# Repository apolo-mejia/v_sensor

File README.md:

# v_sensor
Estos son archivos del sensor de vibraciones desarrollado en el entorno del proyecto Siracuza:
Los archivos que contiene:
- Archivos de diseño electrónico: Esquematicos, planchas de los PCBs y librerias delos componentes,
- Códigos de programación del micro-procesador,
- Archivos de diseño de la carcaza.

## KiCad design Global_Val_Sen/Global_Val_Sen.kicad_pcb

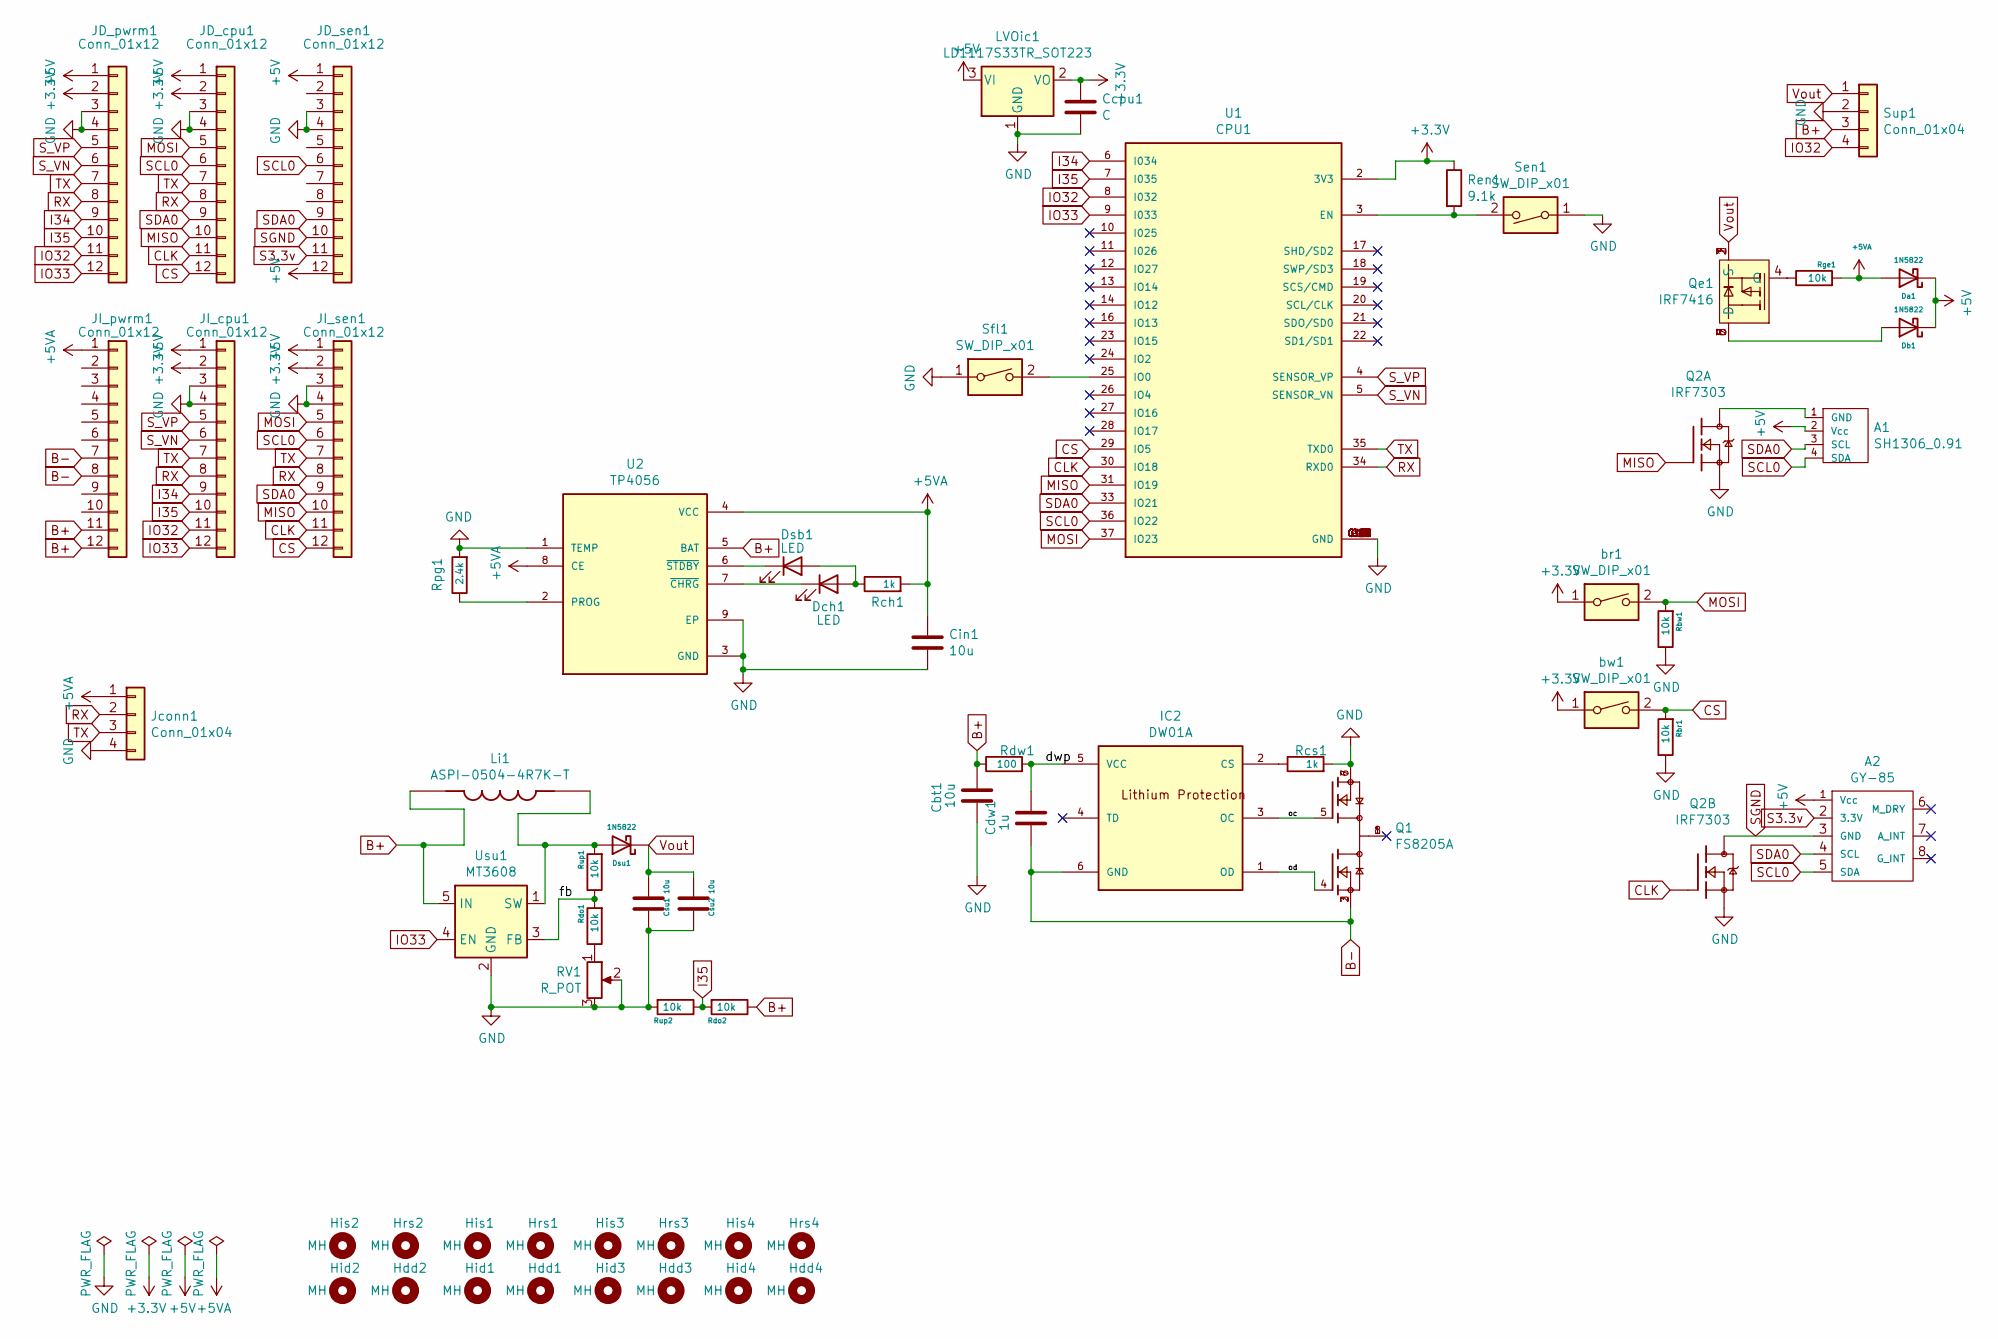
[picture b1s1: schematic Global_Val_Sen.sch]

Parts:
A1: SH1306_0.91; SSD1306-0.91-OLED-4pin-128x32
A2: GY-85
Cbt1: 10u; CP_EIA-3216-10_Kemet-I_Pad1.58x1.35mm_HandSolder
Ccpu1: C; CP_EIA-3216-10_Kemet-I_Pad1.58x1.35mm_HandSolder
Cdw1: 1u; CP_EIA-3216-10_Kemet-I_Pad1.58x1.35mm_HandSolder
Cin1: 10u; CP_EIA-3216-10_Kemet-I_Pad1.58x1.35mm_HandSolder
Csu1, Csu2: 10u; CP_EIA-3216-10_Kemet-I_Pad1.58x1.35mm_HandSolder
Da1: 1N5822; D_SMA
Db1: 1N5822; D_SMA
Dch1: LED; LED_1206_3216Metric_Castellated
Dsb1: LED; LED_1206_3216Metric_Castellated
Dsu1: 1N5822; D_SMA
Hdd1, Hdd2, Hdd3, Hdd4: MH; MountingHole_2.2mm_M2_DIN965
Hid1, Hid2, Hid3, Hid4: MH; MountingHole_2.2mm_M2_DIN965
His1, His2, His3, His4: MH; MountingHole_2.2mm_M2_DIN965
Hrs1, Hrs2, Hrs3, Hrs4: MH; MountingHole_2.2mm_M2_DIN965
IC2: DW01A; SOT-23-6_Handsoldering
JD_cpu1: Conn_01x12; PinSocket_1x12_P2.00mm_Vertical
JD_pwrm1: Conn_01x12; PinSocket_1x12_P2.00mm_Vertical
JD_sen1: Conn_01x12; PinSocket_1x12_P2.00mm_Vertical
JI_cpu1: Conn_01x12; PinSocket_1x12_P2.00mm_Vertical
JI_pwrm1: Conn_01x12; PinSocket_1x12_P2.00mm_Vertical
JI_sen1: Conn_01x12; PinSocket_1x12_P2.00mm_Vertical
Jconn1: Conn_01x04; PinHeader_1x04_P2.00mm_Vertical
LVOic1: LD1117S33TR_SOT223; SOT-223-3_TabPin2
Li1: ASPI-0504-4R7K-T; IND_ASPI-0504-4R7K-T; PARTREV 06.24.13
Q1: FS8205A; SOP65P640X120-8N; PARTREV 1.7
Q2: IRF7303; SOIC-8
Qe1: IRF7416; SO-8_3.9x4.9mm_P1.27mm
RV1: R_POT; Potentiometer_Bourns_TC33X_Vertical
Rbr1: 10k; R_1206_3216Metric_Pad1.30x1.75mm_HandSolder
Rbw1: 10k; R_1206_3216Metric_Pad1.30x1.75mm_HandSolder
Rch1: 1k; R_1206_3216Metric_Pad1.30x1.75mm_HandSolder
Rcs1: 1k; R_1206_3216Metric_Pad1.30x1.75mm_HandSolder
Rdo1, Rdo2: 10k; R_1206_3216Metric_Pad1.30x1.75mm_HandSolder
Rdw1: 100; R_1206_3216Metric_Pad1.30x1.75mm_HandSolder
Ren1: 9.1k; R_1206_3216Metric_Pad1.30x1.75mm_HandSolder
Rge1: 10k; R_1206_3216Metric_Pad1.30x1.75mm_HandSolder
Rpg1: 2.4k; R_1206_3216Metric_Pad1.30x1.75mm_HandSolder
Rup1, Rup2: 10k; R_1206_3216Metric_Pad1.30x1.75mm_HandSolder
Sen1: SW_DIP_x01; SW_SPST_CK_RS282G05A3
Sfl1: SW_DIP_x01; SW_SPST_CK_RS282G05A3
Sup1: Conn_01x04; PinSocket_1x04_P2.54mm_Vertical
U1: CPU1; ESP32-WROOM-32U; PARTREV V1.9
U2: TP4056; SOP127P600X175-9N
Usu1: MT3608; SOT-23-6
br1: SW_DIP_x01; SW_SPST_CK_RS282G05A3
bw1: SW_DIP_x01; SW_SPST_CK_RS282G05A3

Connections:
+3V3: Ccpu1.1, JD_cpu1.2, JD_pwrm1.2, JI_cpu1.2, JI_sen1.2, LVOic1.2 (VO), Ren1.1, U1.2 (3V3), br1.1, bw1.1
+5V: A1.2 (Vcc), A2.1 (Vcc), Da1.1 (K), Db1.1 (K), JD_cpu1.1, JD_pwrm1.1, JD_sen1.1, JD_sen1.12, JI_cpu1.1, JI_sen1.1, LVOic1.3 (VI)
+5VA: Cin1.1, Da1.2 (A), JI_pwrm1.1, Jconn1.1, Rch1.2, Rge1.2, U2.4 (VCC), U2.8 (CE)
/dwp: Cdw1.1, IC2.5 (VCC), Rdw1.2
/fb: Rdo1.2, Rup1.1, Usu1.3 (FB)
/oc: IC2.3 (OC), Q1.5
/od: IC2.1 (OD), Q1.4
B+: Cbt1.1, JI_pwrm1.11, JI_pwrm1.12, Li1.1, Rdo2.1, Rdw1.1, Sup1.3, U2.5 (BAT), Usu1.5 (IN)
B-: Cdw1.2, IC2.6 (GND), JI_pwrm1.7, JI_pwrm1.8, Q1.2, Q1.3
CLK: JD_cpu1.11, JI_sen1.11, Q2.4, U1.30 (IO18)
CS: JD_cpu1.12, JI_sen1.12, Rbr1.2, U1.29 (IO5), bw1.2
GND: Cbt1.2, Ccpu1.2, Cin1.2, Csu1.2, Csu2.2, JD_cpu1.3, JD_cpu1.4, JD_pwrm1.3, JD_pwrm1.4, JD_sen1.3, JD_sen1.4, JI_cpu1.3, JI_cpu1.4, JI_sen1.3, JI_sen1.4, Jconn1.4, LVOic1.1 (GND), Q1.6, Q1.7, Q2.1, Q2.3, RV1.2, RV1.3, Rbr1.1, Rbw1.1, Rcs1.2, Rpg1.2, Rup2.2, Sen1.1, Sfl1.1, Sup1.2, U1.1 (GND), U1.15 (GND), U1.38 (GND), U1.G.1 (GND), U1.G.2 (GND), U1.G.4 (GND), U1.G.5 (GND), U1.G.6 (GND), U1.G.7 (GND), U1.G.8 (GND), U1.G.9 (GND), U1.G.10 (GND), U1.G.11 (GND), U1.G.12 (GND), U1.G.13 (GND), U1.G.14 (GND), U1.G.15 (GND), U1.G.16 (GND), U1.G.17 (GND), U1.G.18 (GND), U1.G.19 (GND), U1.G.20 (GND), U1.G.21 (GND), U1.G.22 (GND), U2.1 (TEMP), U2.3 (GND), U2.9 (EP), Usu1.2 (GND)
I34: JD_pwrm1.9, JI_cpu1.9, U1.6 (I034)
I35: JD_pwrm1.10, JI_cpu1.10, Rdo2.2, Rup2.1, U1.7 (I035)
IO32: JD_pwrm1.11, JI_cpu1.11, Sup1.4, U1.8 (I032)
IO33: JD_pwrm1.12, JI_cpu1.12, U1.9 (I033), Usu1.4 (EN)
MISO: JD_cpu1.10, JI_sen1.10, Q2.2, U1.31 (IO19)
MOSI: JD_cpu1.5, JI_sen1.5, Rbw1.2, U1.37 (IO23), br1.2
unnamed: A1.1 (GND), Q2.7, Q2.8
unnamed: Db1.2 (A), Qe1.5 (D), Qe1.6 (D), Qe1.7 (D), Qe1.8 (D)
unnamed: Dch1.1 (K), U2.7 (~CHRG)
unnamed: Dch1.2 (A), Dsb1.2 (A), Rch1.1
unnamed: Dsb1.1 (K), U2.6 (~STDBY)
unnamed: Dsu1.2 (A), Li1.2, Rup1.2, Usu1.1 (SW)
unnamed: IC2.2 (CS), Rcs1.1
unnamed: Q1.1, Q1.8
unnamed: Qe1.4 (G), Rge1.1
unnamed: RV1.1, Rdo1.1
unnamed: Ren1.2, Sen1.2, U1.3 (EN)
unnamed: Rpg1.1, U2.2 (PROG)
unnamed: Sfl1.2, U1.25 (IO0)
RX: JD_cpu1.8, JD_pwrm1.8, JI_cpu1.8, JI_sen1.8, Jconn1.2, U1.34 (RXD0)
S3.3v: A2.2 (3.3V), JD_sen1.11
SCL0: A1.4 (SDA), A2.5 (SDA), JD_cpu1.6, JD_sen1.6, JI_sen1.6, U1.36 (IO22)
SDA0: A1.3 (SCL), A2.4 (SCL), JD_cpu1.9, JD_sen1.9, JI_sen1.9, U1.33 (IO21)
SGND: A2.3 (GND), JD_sen1.10, Q2.5, Q2.6
S_VN: JD_pwrm1.6, JI_cpu1.6, U1.5 (SENSOR_VN)
S_VP: JD_pwrm1.5, JI_cpu1.5, U1.4 (SENSOR_VP)
TX: JD_cpu1.7, JD_pwrm1.7, JI_cpu1.7, JI_sen1.7, Jconn1.3, U1.35 (TXD0)
Vout: Csu1.1, Csu2.1, Dsu1.1 (K), Qe1.1 (S), Qe1.2 (S), Qe1.3 (S), Sup1.1

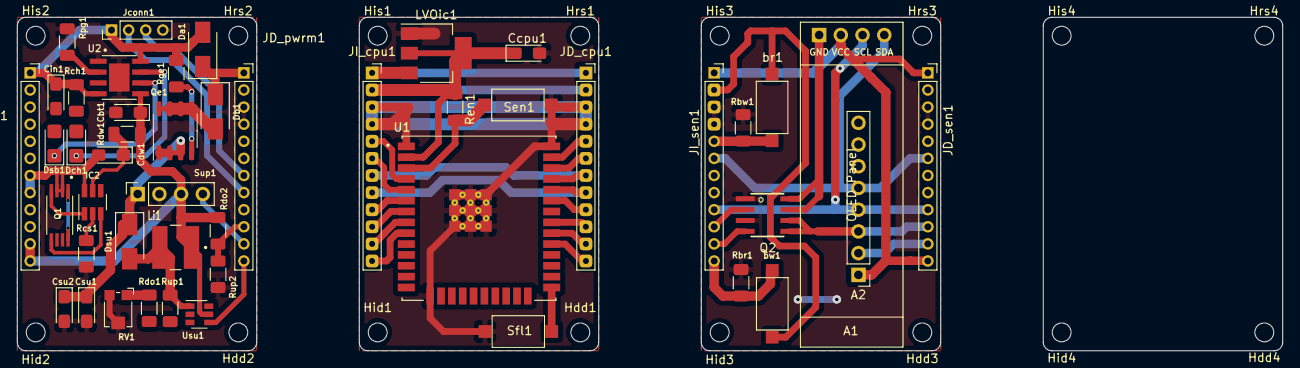
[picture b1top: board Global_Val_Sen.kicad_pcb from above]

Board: 2 copper layers, 148.0 x 39.0 mm, 63 parts (0 on the bottom side), 40 nets.

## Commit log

2022-10-25 Inicial commit
2022-10-29 actualizacion sensor Cod &PCB
